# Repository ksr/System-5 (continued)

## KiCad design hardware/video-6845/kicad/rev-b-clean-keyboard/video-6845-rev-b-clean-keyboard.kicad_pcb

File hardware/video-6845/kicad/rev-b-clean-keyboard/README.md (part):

# 6845 video card Rev B-Clean-Keyboard: KiCad master (2026-11-20)

> **Hand-maintained since 2026-11-20** (`MASTER`), made by `gen/build.sh` from Rev B-Clean's files each run.
> **Not ordered, not built.** Ken, 2026-11-20: "now i want to add keyboard support to Rev B Clean, Call it
> Rev-b-clean-keyboard. Look at video-g for keyboard section only. Expand bus to the 36 pin bus and add jumpers
> required to access keyboard. Rev-b-clean-keyboard and Video-g will never be used at the same time." Asked how the
> CPU should read the keyboard: "Memory-mapped, as VIDEO-G". Later the same day: "ok to grow card if needed", and "it
> is messy to have keyboard and video connector on different edges. Need to move together. Less of an issue for FTDI."
> And: "I would prefer for the power LED to be in the corner like most/all other boards."

Rev B-Clean (`../rev-b-clean/`) is Rev B, the 6845 video card in Ken's machine since 2005, cleaned up for a new order.
This card is Rev B-Clean with a **PS/2 keyboard** on it, so that one card is the whole console: the video as Rev B has
it, and the keyboard section of VIDEO-G TEXT (`hardware/video-g/DESIGN.md`), read the way VIDEO-G's is. It takes the
place of the 2005 IO card's keyboard path (PAK-VI, PIC, CDP1852).

| | Rev B-Clean | Rev B-Clean-Keyboard |
|---|---|---|
| Board | 141.0 x 96.2 mm, 2 layers | **190.5 x 106.565 mm** (7.50 in, the IO panel's length; VIDEO-G TEXT's height), 2 layers: 49.5 mm longer at the front edge for the keyboard section, 10.3 mm more at the +5V end of the bus edge for the six more bus pins |
| Bus connector | 30 pins | **36 pins** (J1): the 30 where they were, then -EF1, -EF2, -EF3, -DMAIN, SC0, -PAUSE |
| The 6845 | answers all of 7800-7FFF (the pair 7800 / 7801, repeated) | **7800 / 7801**, repeated every 8 addresses through 7BFF only; **write-only** (below) |
| Keyboard | none | **PS/2**: an ATmega328P, the key at **7802**, the status at **7804**, KEY-READY also on a bus flag line picked by **JP1** |
| Video jack | RCA on a side edge, where 2005 put it | **RCA at the front edge, under the PS/2 jack** |
| Copper | Rev B's, track for track | Rev B's kept and locked, but for three places (below); the keyboard section's tracks added round it |

## The map (block 7, SV1 as on Rev B)

| Address | Read | Write |
|---|---|---|
| 7000-77FF | the text RAM | the text RAM |
| 7800 / 7801 | nothing (FF on the bus Rev D): the 6845 is write-only | the 6845's address register / data |
| 7802 | **the key**; the read clears KEY-READY (at TPB) | nothing |
| 7804 | **status**: bit 0 KEY-READY, bit 2 VSYNC, bit 3 DE, bit 7 = 1, the rest 0 | nothing |
| 7806, 7C00-7FFF | nothing (VIDEO-G has its mouse, Y register and graphics window there) | nothing |

**The 6845 is write-only** (Ken, 2026-11-24: "Write-only"; [below](#the-6845-is-write-only-2026-11-24)). Nothing of System-5's
reads its registers: not HBIOS, GBASIC or Elf/OS (looked for in the sources, and watched in the emulator). The RAM probes of
HBIOS and of the Elf/OS kernel read 7800, find no RAM there, and need nothing of it. VSYNC and DE are in the status byte.

7800-7807 repeat every 8 addresses through 7BFF. The key and the status are where VIDEO-G TEXT has them, with the same
bits, so **the VIDEO-G HBIOS runs on this card as it is** (`firmware/hbios/video-g`: it polls 7804 and reads 7802). Its
6845 table (64 x 25, eight lines a row, a 1.5 MHz character clock) fits Rev B's hardware too: 9 MHz divided by 6 is
1.5 MHz, and Rev B's character ROM has eight lines a character. In the emulator the monitor comes up on 25 rows and
Elf/OS 5.1.1 boots (below). The machine's own HBIOS (v1.0.x) would show the video but look for keys on port 1.

## Jumpers and connectors

- **SV1 ADDRESS BLOCK**, as on Rev B: one shunt on A15 (pins 1-2) puts the card at 7000.
- **JP1 KBD FLAG** (2 x 4, at the top edge as drawn, by the bus connector's new pins): one shunt picks the bus line
  that KEY-READY pulls low, **-EF1, -EF2, -EF3 or -EF**, or none. The VIDEO-G HBIOS does not need it (it reads the
  status register); a program that tests a flag does. On CPU Rev D the line then goes to whichever of EF1-EF4 that
  card's own jumpers give it.
- **J3**, PS/2 keyboard (Mini-DIN-6), and **J2**, composite video (RCA), side by side at the front edge, mouths at the
  edge. **J4**, the FTDI header for the ATmega's bootloader, lies along the bottom edge as drawn, near the front
  (pin 1 GND at the bus end ... pin 6 DTR, both named on the board).
- **Which backplane:** the 36-pin connector is for the bus Rev D (`hardware/bus/kicad/rev-d`), whose slots have the
  six more positions and pull-ups on -EF1 to -EF3. Pads 1-30 are on Rev B's holes, so with a 30-pin header fitted
  there instead the card is a 30-pin card, flag on -EF only (R11 pulls -EF up on the card). That has not been tried,
  and the card is 10 mm taller than Rev B at that end.

## The keyboard section

It is VIDEO-G TEXT's, part for part and pin for pin (`gen/keyboard.py` has the list), so the ATmega's firmware is the
same sketch, `embedded/video-g-ps2`, in its keyboard mode (PD7 open):

- **IC21 ATmega328P** (Y1 16 MHz) reads the PS/2 keyboard and puts each key's code on MD0-MD7; its LDDATA edge clocks
  the code into **IC19** (74HCT374, the key latch) and sets KEY-READY (**IC18**, half a 74HCT74).
- **IC15** (74HCT138) is the one new decoder: enabled by Rev B's upper-half select (the net that was the 6845's -CS,
  now -UPPER) and A10 low, it picks by A1-A2 the 6845, the key or the status. **IC16** (74HCT32) makes the two read
  enables with -MRD, and the key-read strobe at TPB; **IC17** (74HCT00) inverts TPB and -RESET and makes the
  KEY-READY clear. **IC20** (74HCT244) puts the status on the bus.
- **IC18's other half is the 6845's E** (below).
- **IC22 is a second 7416** (open-collector inverters), for the two jobs VIDEO-G TEXT gives to its 7416, on the same
  gates: one pulls the flag line low while KEY-READY, one pulls the ATmega's reset low while the bus -RESET is low.
  The other four gates' inputs are on ground. Rev B's own 7416 (IC14) has three spare gates, but their inputs are
  tied to ground by copper that carries ground on to other parts, so using them would have meant cutting Rev B's
  ground. The card was first drawn with two 2N7000 transistors there; Ken, 2026-11-20: "swap". A 7406, a 7405 or a
  74HC05 has the same pins and does the same in this socket.
- F1 (0.5 A PTC) feeds the keyboard's +5 V; R8, R9 (4.7k) pull up its clock and data.

Like VIDEO-G TEXT's decoder, IC15 sees the high address byte on A1-A2 early in each cycle. For the addresses the
software uses (7800-7807) that early pick is the 6845, whose E (CRTE) is still low; KEY-READY is cleared only at TPB.

## The 6845 is write-only (2026-11-24)

Rev B wires the 6845's R/W to -MRW and its E to TPB. Two faults come with that (`hardware/TIMING-REVIEW.md`, T2; the first
was seen on the bus of the built card):

- **F1:** -MRW rises half a clock before TPB falls, so every register write ends in a read: the 6845 and the 1802 both
  drive the data bus, and a 6845 that takes its byte when E falls is not written at all.
- **F2:** nothing of -MRD is in its select, so it drives the bus at TPB of a cycle with no memory access (GLO, GHI, PLO,
  PHI, SEP, SEX) when that register points at it.

Ken, 2026-11-24: "Fix both boards", and, asked whether to keep the register reads: "Write-only". On this card:

- **R/W (IC3 pin 22) is on ground**, and **E (pin 23) is CRTE = NOT -MRW**: high for the whole write strobe, 5 T to 7 T,
  and at no other time. So the 6845 never drives the bus, whatever the cycle.
- CRTE is **IC18A**, the spare half of the KEY-READY 74HCT74, as an inverter: its -CLR (pin 1) on ground and -MRW on its
  -PRE (pin 4) make Q (pin 5) high while -MRW is low and low otherwise. It has no state to power up in. (Its D and clock stay
  on ground.)
- E is two clocks long and the data stays until T - 200 ns past it, so **every grade on the two data sheets here will do, at 2 MHz too**
  (Motorola's 1 MHz part, Hitachi's 1, 1.5 and 2 MHz). Motorola's allows E high for 25 us at most, Hitachi's has no limit: a pause, stepping and the bus driver hold it longer
  (`hardware/TIMING-REVIEW.md`, "E held high"). From the netlist
  at 2 MHz, worst case (`python3 -m s5emu.timing --crtc B-Clean-Keyboard 2`): E's width +406 ns for a 1 MHz 6845 (+636 for an HD68B45), data
  hold +246, data set-up +2055, address set-up +895.
- `software/s5emu/tests/test_hw_crtcbus.py` holds it: the two faults' tests fail on the card as first drawn and pass here,
  and nine wrong wires of the change are each caught.

The register reads that are lost (R14-R17) were never used; on the 1 MHz part they were late by 77 ns in the worst case.

## Where Rev B's copper was touched

Of Rev B-Clean's 1,415 tracks and vias, 1,390 are where 2005 put them, locked, and `gen/make_board.py` stops if any
pad of Rev B's would change its net. The other 25:

1. **The 6845's select** (5 pieces). Rev B's track from IC5 pin 3 to IC3 pin 25 is cut at IC5: the pin now drives
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
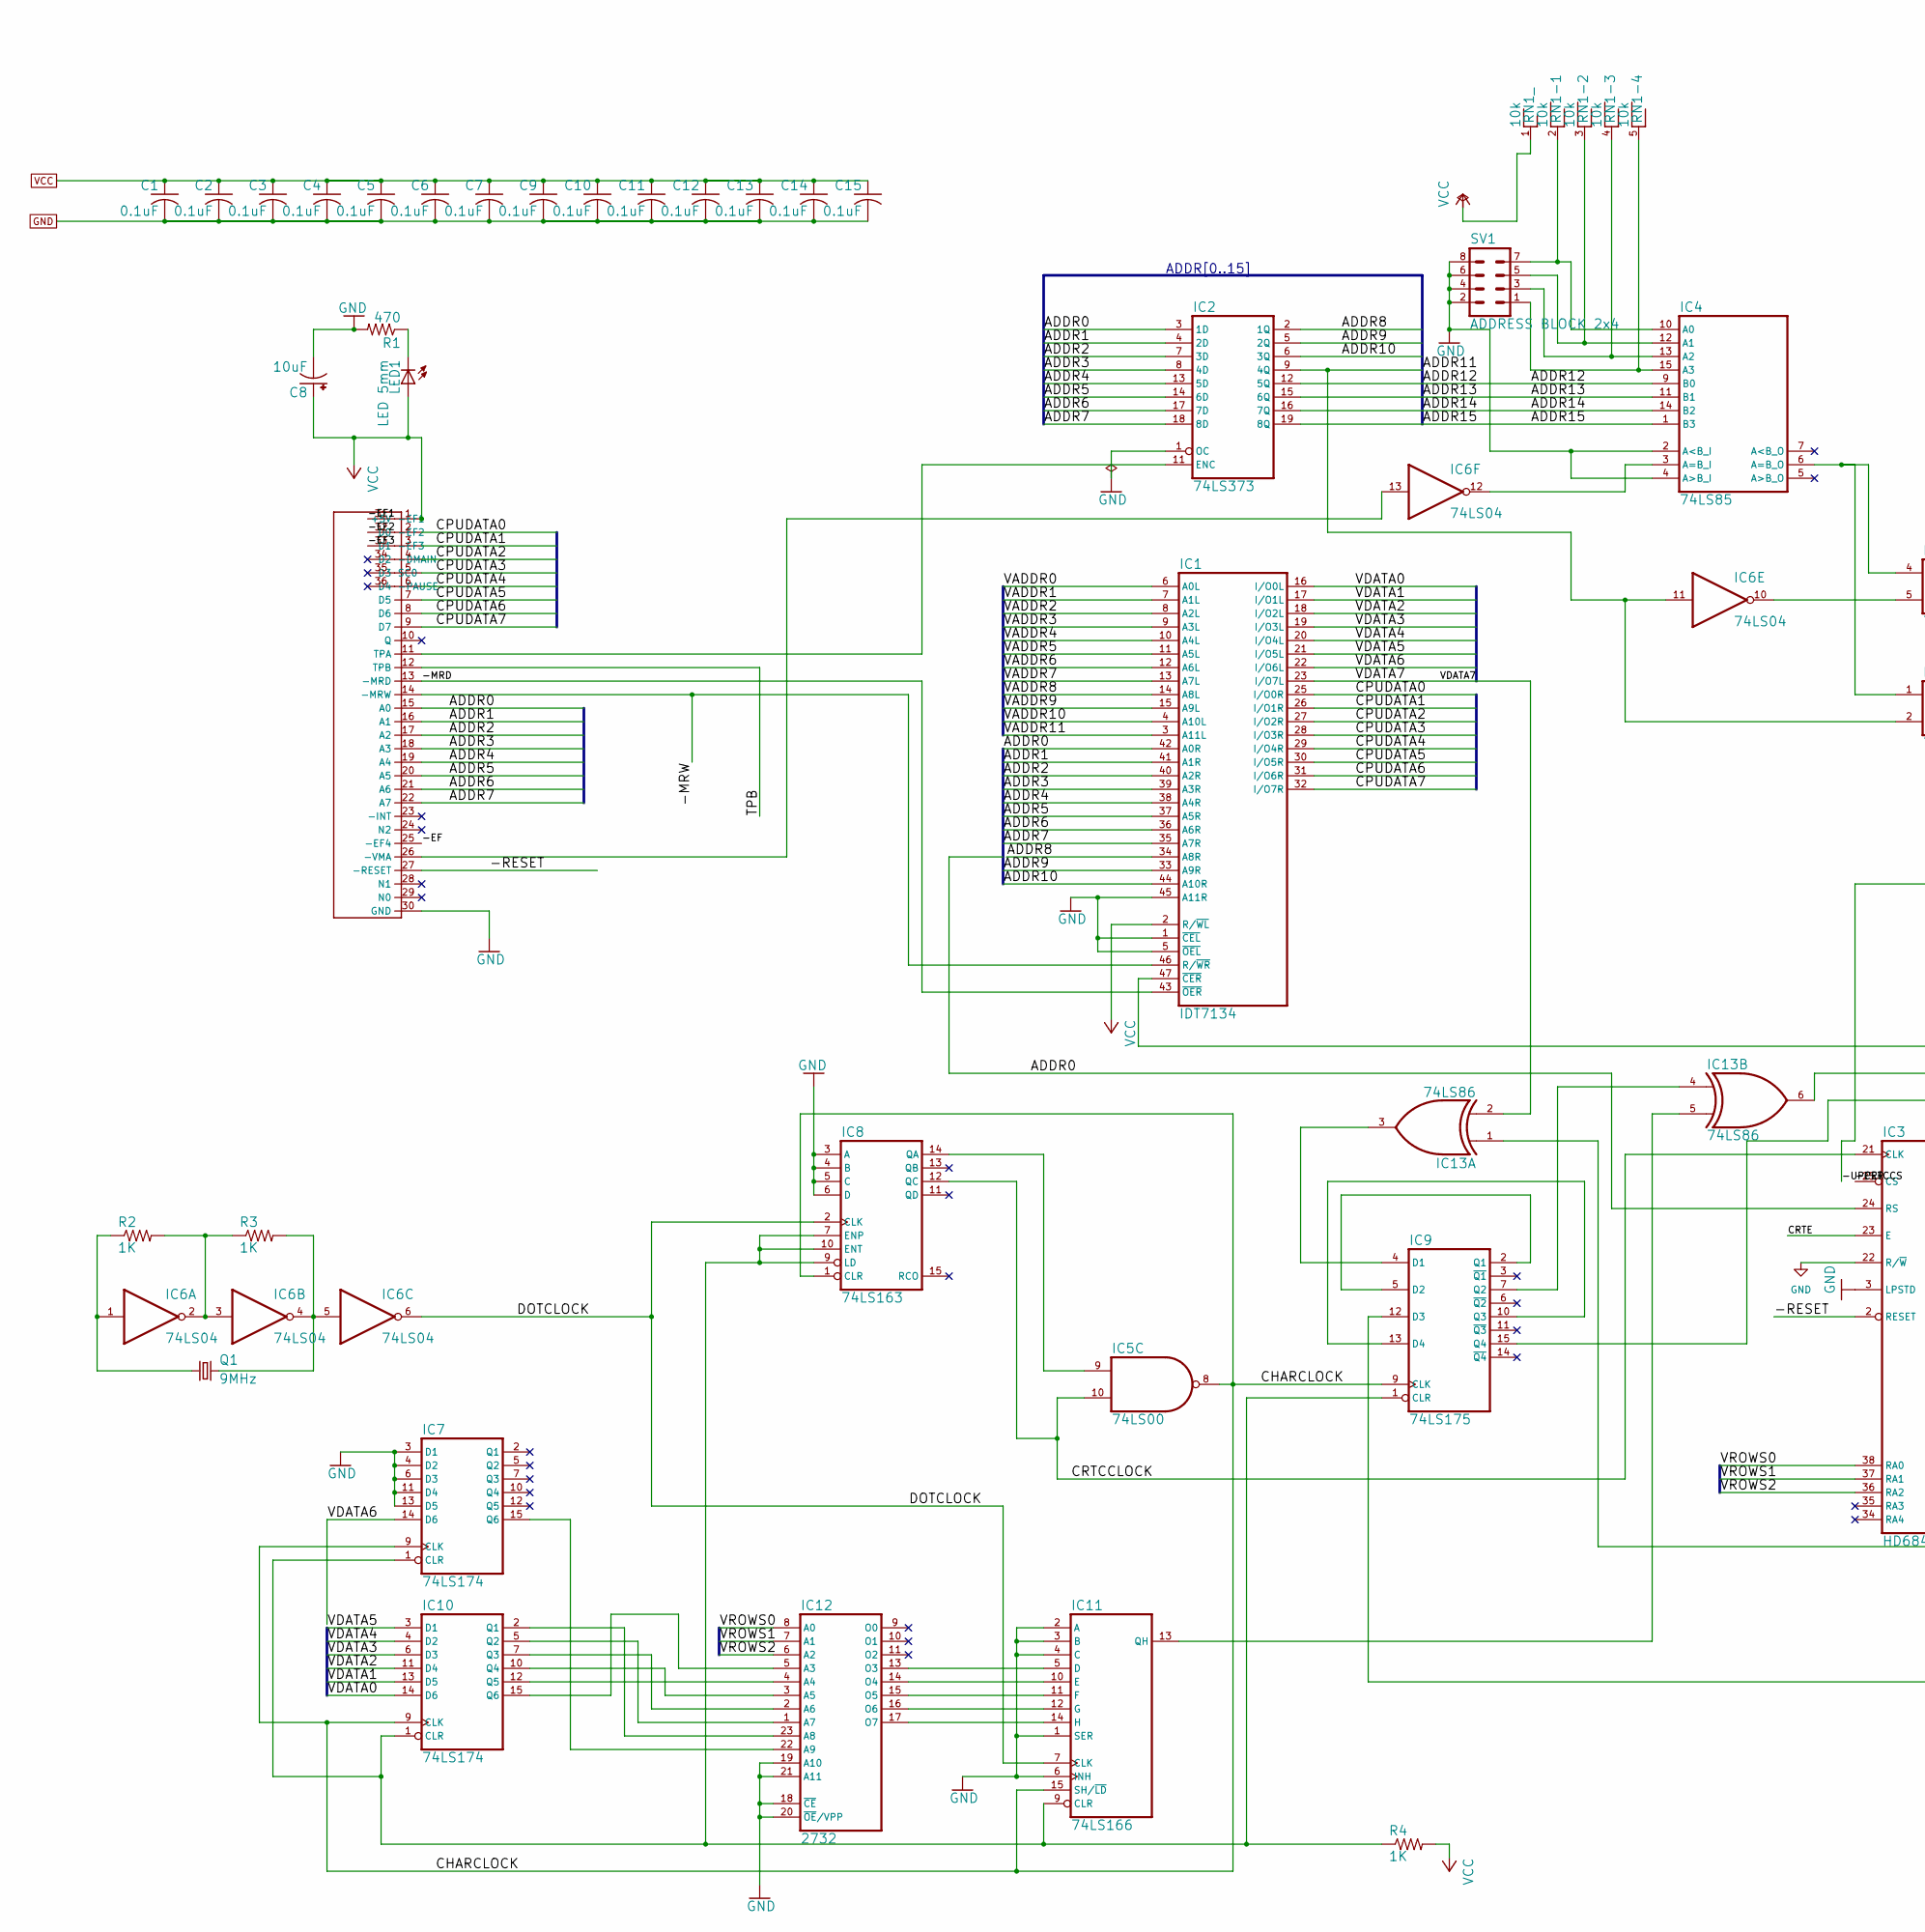
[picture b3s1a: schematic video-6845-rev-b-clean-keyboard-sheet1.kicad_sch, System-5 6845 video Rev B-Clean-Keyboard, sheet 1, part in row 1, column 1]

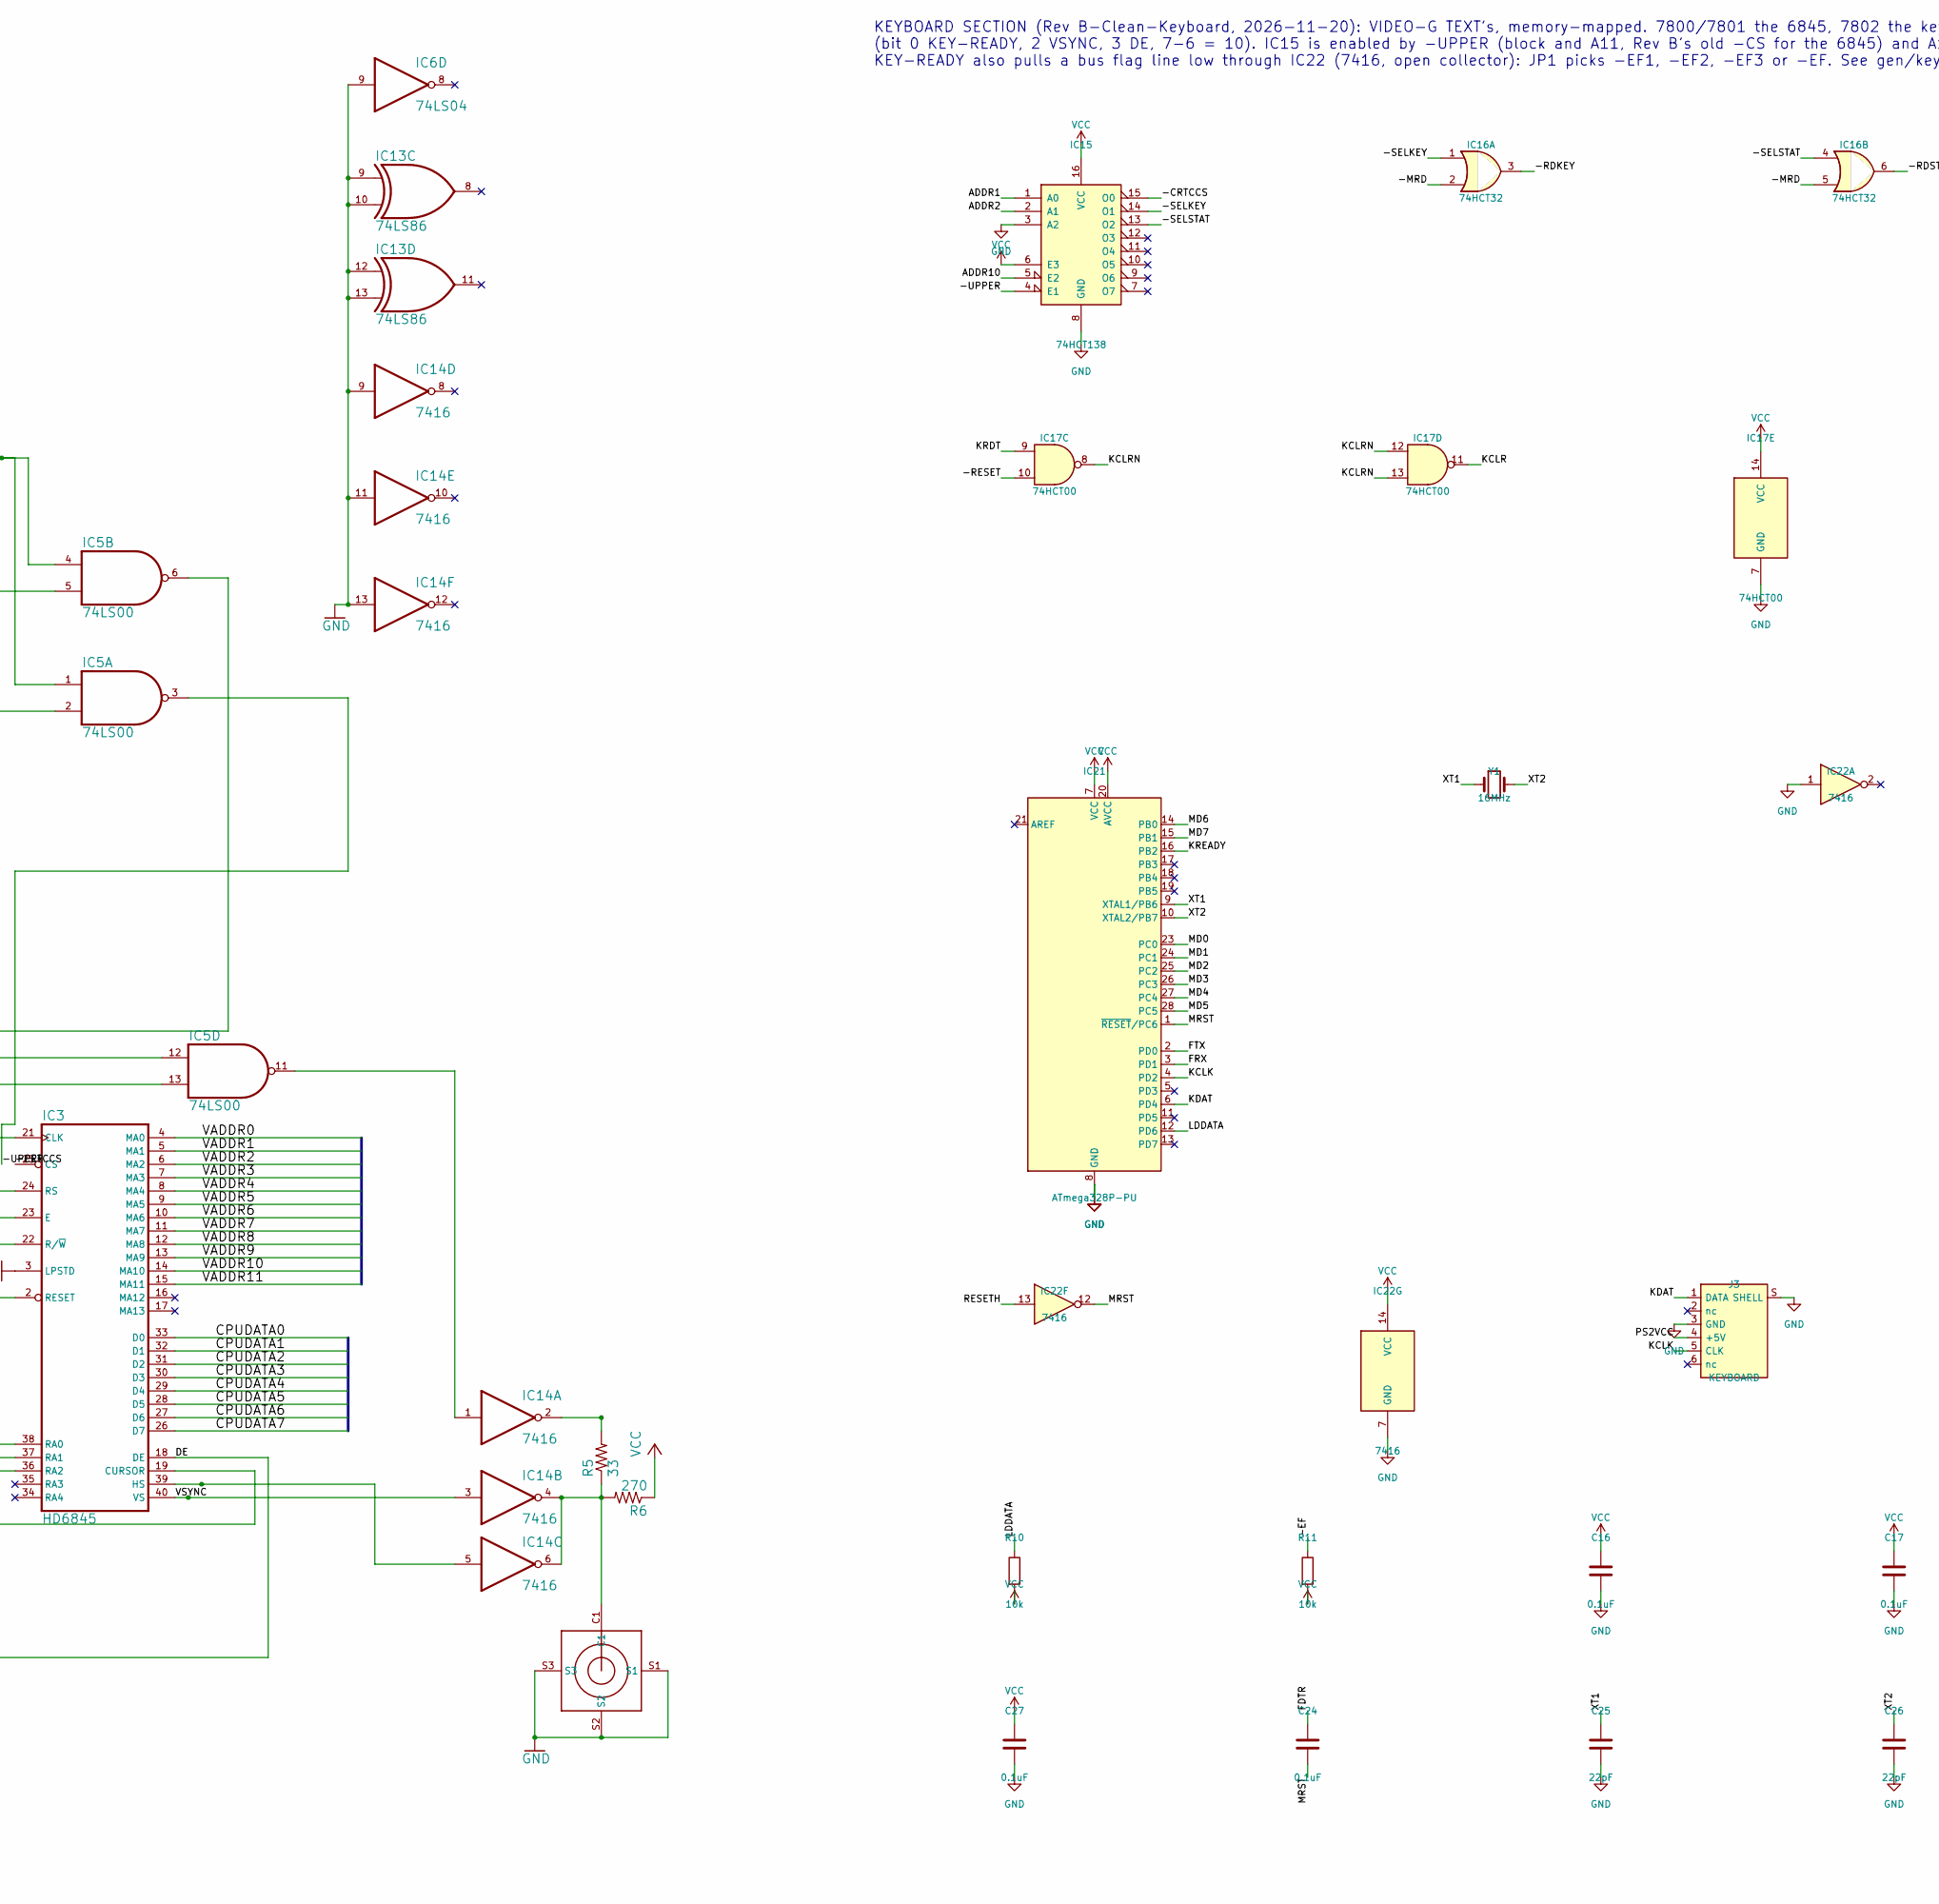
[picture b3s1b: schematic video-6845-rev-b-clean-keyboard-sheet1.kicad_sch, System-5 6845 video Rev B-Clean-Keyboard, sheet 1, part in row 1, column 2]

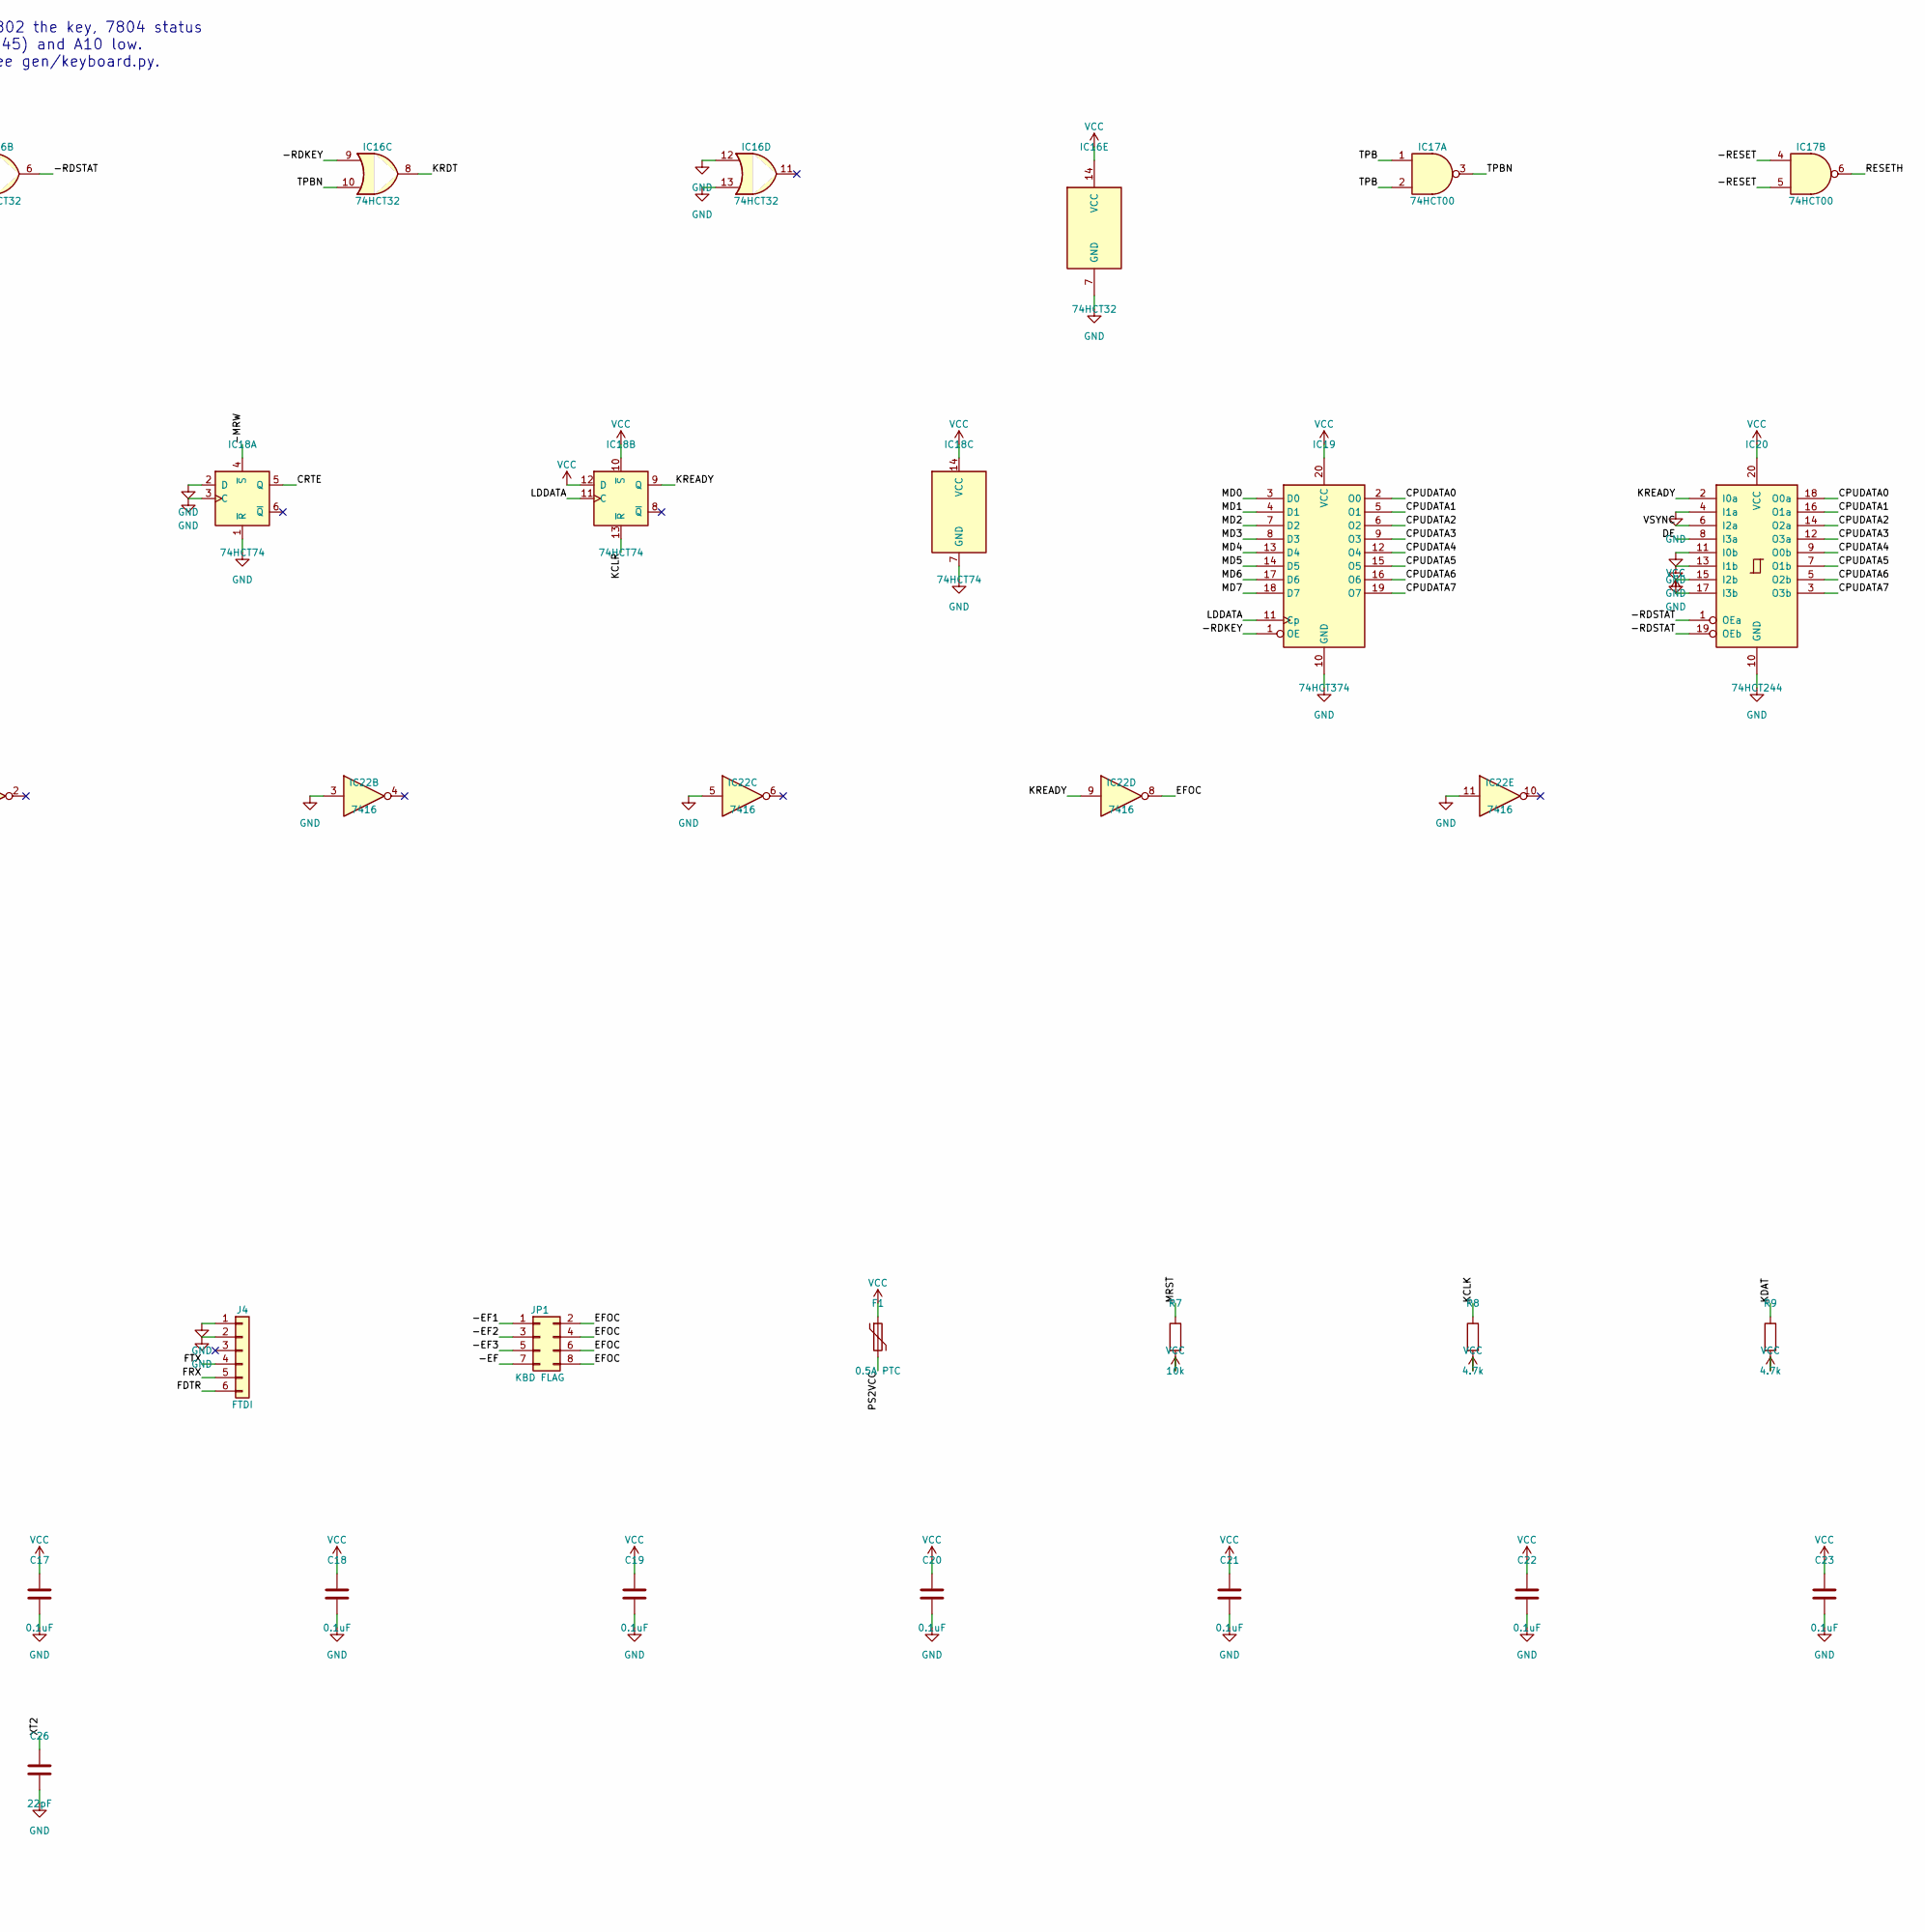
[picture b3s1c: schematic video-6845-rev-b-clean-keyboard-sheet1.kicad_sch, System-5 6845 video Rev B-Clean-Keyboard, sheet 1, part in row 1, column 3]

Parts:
C1, C2, C3, C4, C5, C6, C7, C9, C10, C11, C12, C13, C14, C15, C16, C17, C18, C19, C20, C21, C22, C23, C24, C27: 0.1uF; C025-050X050
C8: 10uF; E2,5-7
C25, C26: 22pF; C025-050X050
F1: 0.5A PTC; Fuse_Bourns_MF-RHT050
IC1: IDT7134; DIL48
IC2: 74LS373; DIL20
IC3: HD6845; DIL40
IC4: 74LS85; DIL16
IC5: 74LS00; DIL14
IC6: 74LS04; DIL14
IC7, IC10: 74LS174; DIL16
IC8: 74LS163; DIL16
IC9: 74LS175; DIL16
IC11: 74LS166; DIL16
IC12: 2732; DIL24
IC13: 74LS86; DIL14
IC14: 7416; DIL14
IC15: 74HCT138; DIP-16_W7.62mm_Socket
IC16: 74HCT32; DIP-14_W7.62mm_Socket
IC17: 74HCT00; DIP-14_W7.62mm_Socket
IC18: 74HCT74; DIP-14_W7.62mm_Socket
IC19: 74HCT374; DIP-20_W7.62mm_Socket
IC20: 74HCT244; DIP-20_W7.62mm_Socket
IC21: ATmega328P-PU; DIP-28_W7.62mm_Socket
IC22: 7416; DIP-14_W7.62mm_Socket
J1: System-5 bus 36-pin; C36
J2: RCA jack; RCA
J3: KEYBOARD; MiniDIN6_MD-60SM
J4: FTDI; PinHeader_1x06_P2.54mm_Vertical
JP1: KBD FLAG; PinHeader_2x04_P2.54mm_Vertical
LED1: LED 5mm; LED5MM
Q1: 9MHz; HC49U-V
R1: 470; 0207_7
R2, R3, R4: 1K; 0207_7
R5: 33; 0207_7
R6: 270; 0207_7
R7, R10, R11: 10k; R_Axial_DIN0207_L6.3mm_D2.5mm_P2.54mm_Vertical
R8, R9: 4.7k; R_Axial_DIN0207_L6.3mm_D2.5mm_P2.54mm_Vertical
RN1: 10k; RN-5
SV1: ADDRESS BLOCK 2x4; MA04-2
Y1: 16MHz; Crystal_HC49-U_Vertical

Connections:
/Sheet 1/-CRTCCS: IC3.25 (CS), IC15.15 (O0)
/Sheet 1/-EF: J1.25 (-EF4), JP1.7, R11.1
/Sheet 1/-EF1: J1.31 (-EF1), JP1.1
/Sheet 1/-EF2: J1.32 (-EF2), JP1.3
/Sheet 1/-EF3: J1.33 (-EF3), JP1.5
/Sheet 1/-MRD: IC1.43 (~OER), IC16.2, IC16.5, J1.13 (-MRD)
/Sheet 1/-MRW: IC1.46 (R/~WR), IC18.4 (~S), J1.14 (-MRW)
/Sheet 1/-RDKEY: IC16.3, IC16.9, IC19.1 (OE)
/Sheet 1/-RDSTAT: IC16.6, IC20.1 (OEa), IC20.19 (OEb)
/Sheet 1/-RESET: IC3.2 (RESET), IC17.4, IC17.5, IC17.10, J1.27 (-RESET)
/Sheet 1/-SELKEY: IC15.14 (O1), IC16.1
/Sheet 1/-SELSTAT: IC15.13 (O2), IC16.4
/Sheet 1/-UPPER: IC5.3 (O), IC15.4 (E1)
/Sheet 1/ADDR0: IC1.42 (A0R), IC2.3 (1D), IC3.24 (RS), J1.15 (A0)
/Sheet 1/ADDR1: IC1.41 (A1R), IC2.4 (2D), IC15.1 (A0), J1.16 (A1)
/Sheet 1/ADDR2: IC1.40 (A2R), IC2.7 (3D), IC15.2 (A1), J1.17 (A2)
/Sheet 1/ADDR3: IC1.39 (A3R), IC2.8 (4D), J1.18 (A3)
/Sheet 1/ADDR4: IC1.38 (A4R), IC2.13 (5D), J1.19 (A4)
/Sheet 1/ADDR5: IC1.37 (A5R), IC2.14 (6D), J1.20 (A5)
/Sheet 1/ADDR6: IC1.36 (A6R), IC2.17 (7D), J1.21 (A6)
/Sheet 1/ADDR7: IC1.35 (A7R), IC2.18 (8D), J1.22 (A7)
/Sheet 1/ADDR8: IC1.34 (A8R), IC2.2 (1Q)
/Sheet 1/ADDR9: IC1.33 (A9R), IC2.5 (2Q)
/Sheet 1/ADDR10: IC1.44 (A10R), IC2.6 (3Q), IC15.5 (E2)
/Sheet 1/ADDR11: IC2.9 (4Q), IC5.2 (I1), IC6.11 (I)
/Sheet 1/ADDR12: IC2.12 (5Q), IC4.9 (B0)
/Sheet 1/ADDR13: IC2.15 (6Q), IC4.11 (B1)
/Sheet 1/ADDR14: IC2.16 (7Q), IC4.14 (B2)
/Sheet 1/ADDR15: IC2.19 (8Q), IC4.1 (B3)
/Sheet 1/CHARCLOCK: IC5.8 (O), IC7.9 (CLK), IC8.1 (CLR), IC9.9 (CLK), IC10.9 (CLK), IC11.15 (SH/~LD)
/Sheet 1/CPUDATA0: IC1.25 (I/O0R), IC3.33 (D0), IC19.2 (O0), IC20.18 (O0a), J1.2 (D0)
/Sheet 1/CPUDATA1: IC1.26 (I/O1R), IC3.32 (D1), IC19.5 (O1), IC20.16 (O1a), J1.3 (D1)
/Sheet 1/CPUDATA2: IC1.27 (I/O2R), IC3.31 (D2), IC19.6 (O2), IC20.14 (O2a), J1.4 (D2)
/Sheet 1/CPUDATA3: IC1.28 (I/O3R), IC3.30 (D3), IC19.9 (O3), IC20.12 (O3a), J1.5 (D3)
/Sheet 1/CPUDATA4: IC1.29 (I/O4R), IC3.29 (D4), IC19.12 (O4), IC20.9 (O0b), J1.6 (D4)
/Sheet 1/CPUDATA5: IC1.30 (I/O5R), IC3.28 (D5), IC19.15 (O5), IC20.7 (O1b), J1.7 (D5)
/Sheet 1/CPUDATA6: IC1.31 (I/O6R), IC3.27 (D6), IC19.16 (O6), IC20.5 (O2b), J1.8 (D6)
/Sheet 1/CPUDATA7: IC1.32 (I/O7R), IC3.26 (D7), IC19.19 (O7), IC20.3 (O3b), J1.9 (D7)
/Sheet 1/CRTCCLOCK: IC3.21 (CLK), IC5.10 (I1), IC8.12 (QC)
/Sheet 1/CRTE: IC3.23 (E), IC18.5 (Q)
/Sheet 1/DE: IC3.18 (DE), IC9.12 (D3), IC20.8 (I3a)
/Sheet 1/DOTCLOCK: IC6.6 (O), IC8.2 (CLK), IC11.7 (CLK)
/Sheet 1/EFOC: IC22.8, JP1.2, JP1.4, JP1.6, JP1.8
/Sheet 1/FDTR: C24.1, J4.6
/Sheet 1/FRX: IC21.3 (PD1), J4.5
/Sheet 1/FTX: IC21.2 (PD0), J4.4
/Sheet 1/KCLK: IC21.4 (PD2), J3.5 (CLK), R8.1
/Sheet 1/KCLR: IC17.11, IC18.13 (~R)
/Sheet 1/KCLRN: IC17.8, IC17.12, IC17.13
/Sheet 1/KDAT: IC21.6 (PD4), J3.1 (DATA), R9.1
/Sheet 1/KRDT: IC16.8, IC17.9
/Sheet 1/KREADY: IC18.9 (Q), IC20.2 (I0a), IC21.16 (PB2), IC22.9
/Sheet 1/LDDATA: IC18.11 (C), IC19.11 (Cp), IC21.12 (PD6), R10.1
/Sheet 1/MD0: IC19.3 (D0), IC21.23 (PC0)
/Sheet 1/MD1: IC19.4 (D1), IC21.24 (PC1)
/Sheet 1/MD2: IC19.7 (D2), IC21.25 (PC2)
/Sheet 1/MD3: IC19.8 (D3), IC21.26 (PC3)
/Sheet 1/MD4: IC19.13 (D4), IC21.27 (PC4)
/Sheet 1/MD5: IC19.14 (D5), IC21.28 (PC5)
/Sheet 1/MD6: IC19.17 (D6), IC21.14 (PB0)
/Sheet 1/MD7: IC19.18 (D7), IC21.15 (PB1)
/Sheet 1/MRST: C24.2, IC21.1 (~RESET/PC6), IC22.12, R7.1
/Sheet 1/PS2VCC: F1.2, J3.4 (+5V)
/Sheet 1/RESETH: IC17.6, IC22.13
/Sheet 1/TPB: IC17.1, IC17.2, J1.12 (TPB)
/Sheet 1/TPBN: IC16.10, IC17.3
/Sheet 1/VADDR0: IC1.6 (A0L), IC3.4 (MA0)
/Sheet 1/VADDR1: IC1.7 (A1L), IC3.5 (MA1)
/Sheet 1/VADDR2: IC1.8 (A2L), IC3.6 (MA2)
/Sheet 1/VADDR3: IC1.9 (A3L), IC3.7 (MA3)
/Sheet 1/VADDR4: IC1.10 (A4L), IC3.8 (MA4)
/Sheet 1/VADDR5: IC1.11 (A5L), IC3.9 (MA5)
/Sheet 1/VADDR6: IC1.12 (A6L), IC3.10 (MA6)
/Sheet 1/VADDR7: IC1.13 (A7L), IC3.11 (MA7)
/Sheet 1/VADDR8: IC1.14 (A8L), IC3.12 (MA8)
/Sheet 1/VADDR9: IC1.15 (A9L), IC3.13 (MA9)
/Sheet 1/VADDR10: IC1.4 (A10L), IC3.14 (MA10)
/Sheet 1/VADDR11: IC1.3 (A11L), IC3.15 (MA11)
/Sheet 1/VDATA0: IC1.16 (I/O0L), IC10.14 (D6)
/Sheet 1/VDATA1: IC1.17 (I/O1L), IC10.13 (D5)
/Sheet 1/VDATA2: IC1.18 (I/O2L), IC10.11 (D4)
/Sheet 1/VDATA3: IC1.19 (I/O3L), IC10.6 (D3)
/Sheet 1/VDATA4: IC1.20 (I/O4L), IC10.4 (D2)
/Sheet 1/VDATA5: IC1.21 (I/O5L), IC10.3 (D1)
/Sheet 1/VDATA6: IC1.22 (I/O6L), IC7.14 (D6)
/Sheet 1/VDATA7: IC1.23 (I/O7L), IC13.2 (I1)
/Sheet 1/VROWS0: IC3.38 (RA0), IC12.8 (A0)
/Sheet 1/VROWS1: IC3.37 (RA1), IC12.7 (A1)
/Sheet 1/VROWS2: IC3.36 (RA2), IC12.6 (A2)
/Sheet 1/VSYNC: IC3.40 (VS), IC14.3 (I), IC20.6 (I2a)
/Sheet 1/XT1: C25.1, IC21.9 (XTAL1/PB6), Y1.1
/Sheet 1/XT2: C26.1, IC21.10 (XTAL2/PB7), Y1.2
GND: C1.2, C2.2, C3.2, C4.2, C5.2, C6.2, C7.2, C8.-, C9.2, C10.2, C11.2, C12.2, C13.2, C14.2, C15.2, C16.2, C17.2, C18.2, C19.2, C20.2, C21.2, C22.2, C23.2, C25.2, C26.2, C27.2, IC1.1 (~CEL), IC1.5 (~OEL), IC1.24 (GND), IC1.45 (A11R), IC2.1 (OC), IC2.10 (GND), IC3.1 (GND), IC3.3 (LPSTD), IC3.22 (R/~W), IC4.2 (A<B_I), IC4.4 (A>B_I), IC4.8 (GND), IC5.7 (GND), IC6.7 (GND), IC6.9 (I), IC7.3 (D1), IC7.4 (D2), IC7.6 (D3), IC7.8 (GND), IC7.11 (D4), IC7.13 (D5), IC8.3 (A), IC8.4 (B), IC8.5 (C), IC8.6 (D), IC8.8 (GND), IC9.8 (GND), IC10.8 (GND), IC11.1 (SER), IC11.2 (A), IC11.3 (B), IC11.4 (C), IC11.6 (INH), IC11.8 (GND), IC12.12 (GND), IC12.18 (~CE), IC12.19 (A10), IC12.20 (~OE/VPP), IC12.21 (A11), IC13.7 (GND), IC13.9 (I0), IC13.10 (I1), IC13.12 (I0), IC13.13 (I1), IC14.7 (GND), IC14.9 (I), IC14.11 (I), IC14.13 (I), IC15.3 (A2), IC15.8 (GND), IC16.7 (GND), IC16.12, IC16.13, IC17.7 (GND), IC18.1 (~R), IC18.2 (D), IC18.3 (C), IC18.7 (GND), IC19.10 (GND), IC20.4 (I1a), IC20.10 (GND), IC20.11 (I0b), IC20.13 (I1b), IC20.15 (I2b), IC21.8 (GND), IC21.22 (GND), IC22.1, IC22.3, IC22.5, IC22.7 (GND), IC22.11, J1.30 (GND), J2.S1, J2.S2, J2.S3, J3.3 (GND), J3.S (SHELL), J4.1, J4.2, R1.2, SV1.2, SV1.4, SV1.6, SV1.8
unnamed: IC1.47 (~CER), IC5.6 (O)
unnamed: IC2.11 (ENC), J1.11 (TPA)
unnamed: IC4.10 (A0), RN1.2, SV1.7
unnamed: IC4.12 (A1), RN1.3, SV1.5
unnamed: IC4.13 (A2), RN1.4, SV1.3
unnamed: IC4.15 (A3), RN1.5, SV1.1
unnamed: IC4.3 (A=B_I), IC6.12 (O)
unnamed: IC4.6 (A=B_O), IC5.1 (I0), IC5.4 (I0)
unnamed: IC5.5 (I1), IC6.10 (O)
unnamed: IC5.9 (I0), IC8.14 (QA)
unnamed: IC5.13 (I1), IC9.15 (Q4)
unnamed: IC6.1 (I), Q1.1, R2.1
unnamed: IC6.2 (O), IC6.3 (I), R2.2, R3.1
unnamed: IC6.4 (O), IC6.5 (I), Q1.2, R3.2
unnamed: IC6.13 (I), J1.26 (-VMA)
unnamed: IC9.2 (Q1), IC9.5 (D2)
unnamed: IC9.10 (Q3), IC9.13 (D4)
unnamed: IC7.1 (CLR), IC8.7 (ENP), IC8.9 (LD), IC8.10 (ENT), IC9.1 (CLR), IC10.1 (CLR), IC11.9 (CLR), R4.1
unnamed: IC10.2 (Q1), IC12.23 (A8)
unnamed: IC10.5 (Q2), IC12.1 (A7)
unnamed: IC10.7 (Q3), IC12.2 (A6)
unnamed: IC10.10 (Q4), IC12.3 (A5)
unnamed: IC10.12 (Q5), IC12.4 (A4)
unnamed: IC10.15 (Q6), IC12.5 (A3)
unnamed: IC11.5 (D), IC12.13 (O3)
unnamed: IC11.10 (E), IC12.14 (O4)
unnamed: IC11.11 (F), IC12.15 (O5)
unnamed: IC11.12 (G), IC12.16 (O6)
unnamed: IC11.14 (H), IC12.17 (O7)
unnamed: IC11.13 (QH), IC13.5 (I1)
unnamed: IC7.15 (Q6), IC12.22 (A9)
unnamed: IC3.19 (CURSOR), IC13.1 (I0)
unnamed: IC9.4 (D1), IC13.3 (O)
unnamed: IC9.7 (Q2), IC13.4 (I0)
unnamed: IC5.12 (I0), IC13.6 (O)
unnamed: IC5.11 (O), IC14.1 (I)
unnamed: IC14.2 (O), R5.2
unnamed: IC14.4 (O), IC14.6 (O), J2.C1, R5.1, R6.2
unnamed: IC3.39 (HS), IC14.5 (I)
unnamed: LED1.K (C), R1.1
VCC: C1.1, C2.1, C3.1, C4.1, C5.1, C6.1, C7.1, C8.+, C9.1, C10.1, C11.1, C12.1, C13.1, C14.1, C15.1, C16.1, C17.1, C18.1, C19.1, C20.1, C21.1, C22.1, C23.1, C27.1, F1.1, IC1.2 (R/~WL), IC1.48 (VCC), IC2.20 (VCC), IC3.20 (VCC), IC4.16 (VCC), IC5.14 (VCC), IC6.14 (VCC), IC7.16 (VCC), IC8.16 (VCC), IC9.16 (VCC), IC10.16 (VCC), IC11.16 (VCC), IC12.24 (VCC), IC13.14 (VCC), IC14.14 (VCC), IC15.6 (E3), IC15.16 (VCC), IC16.14 (VCC), IC17.14 (VCC), IC18.10 (~S), IC18.12 (D), IC18.14 (VCC), IC19.20 (VCC), IC20.17 (I3b), IC20.20 (VCC), IC21.7 (VCC), IC21.20 (AVCC), IC22.14 (VCC), J1.1 (+5V), LED1.A, R4.2, R6.1, R7.2, R8.2, R9.2, R10.2, R11.2, RN1.1

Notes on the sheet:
ADDR[0..15]
KEYBOARD SECTION (Rev B-Clean-Keyboard, 2026-11-20): VIDEO-G TEXT's, memory-mapped. 7800/7801 the 6845, 7802 the key, 7804 status
(bit 0 KEY-READY, 2 VSYNC, 3 DE, 7-6 = 10). IC15 is enabled by -UPPER (block and A11, Rev B's old -CS for the 6845) and A10 low.
KEY-READY also pulls a bus flag line low through IC22 (7416, open collector): JP1 picks -EF1, -EF2, -EF3 or -EF. See gen/keyboard.py.

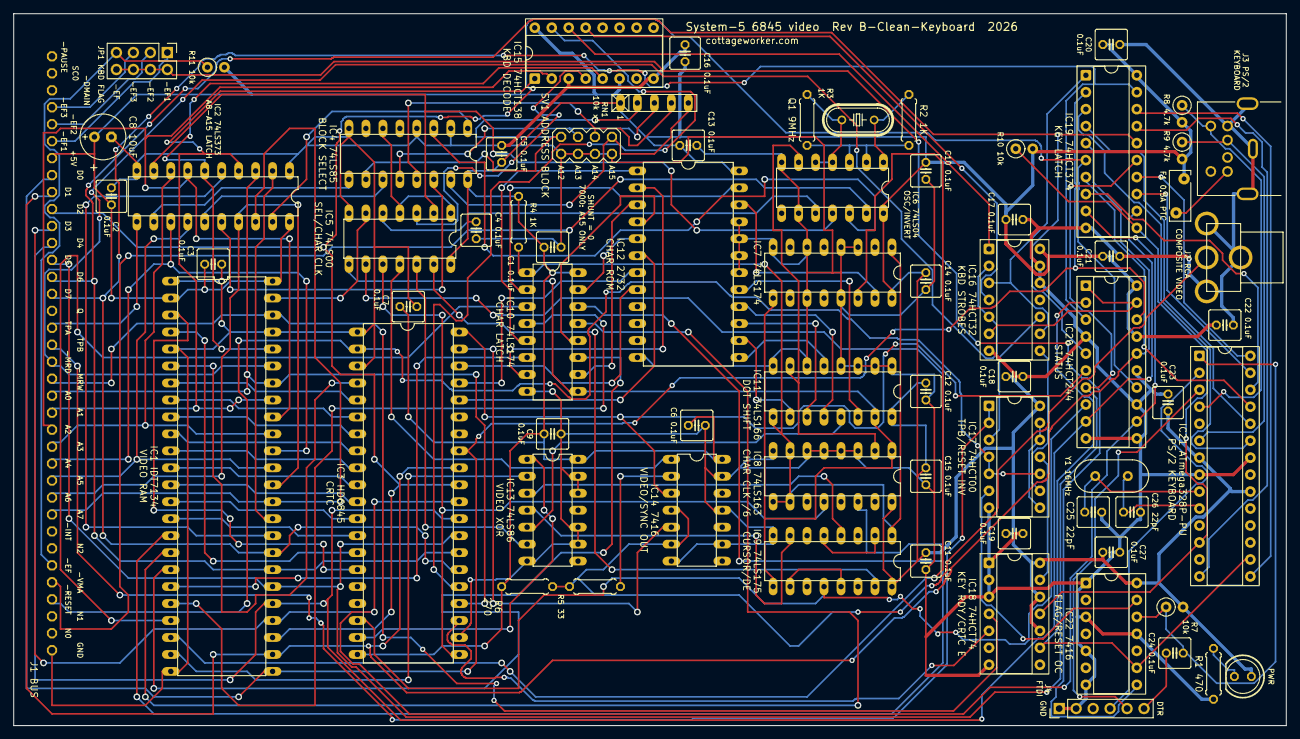
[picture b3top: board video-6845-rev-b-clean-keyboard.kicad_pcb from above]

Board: 2 copper layers, 190.5 x 106.6 mm, 71 parts (0 on the bottom side), 134 nets.

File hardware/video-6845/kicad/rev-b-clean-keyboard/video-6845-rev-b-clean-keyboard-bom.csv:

"Reference","Value","Footprint","QUANTITY"
"C1-C7,C9-C24,C27","0.1uF","video-6845-rev-b-clean-keyboard-eagle:C025-050X050","24"
"C8","10uF","video-6845-rev-b-clean-keyboard-eagle:E2,5-7","1"
"C25,C26","22pF","video-6845-rev-b-clean-keyboard-eagle:C025-050X050","2"
"F1","0.5A PTC","Fuse:Fuse_Bourns_MF-RHT050","1"
"IC1","IDT7134","video-6845-rev-b-clean-keyboard-eagle:DIL48","1"
"IC2","74LS373","video-6845-rev-b-clean-keyboard-eagle:DIL20","1"
"IC3","HD6845","video-6845-rev-b-clean-keyboard-eagle:DIL40","1"
"IC4","74LS85","video-6845-rev-b-clean-keyboard-eagle:DIL16","1"
"IC5","74LS00","video-6845-rev-b-clean-keyboard-eagle:DIL14","1"
"IC6","74LS04","video-6845-rev-b-clean-keyboard-eagle:DIL14","1"
"IC7,IC10","74LS174","video-6845-rev-b-clean-keyboard-eagle:DIL16","2"
"IC8","74LS163","video-6845-rev-b-clean-keyboard-eagle:DIL16","1"
"IC9","74LS175","video-6845-rev-b-clean-keyboard-eagle:DIL16","1"
"IC11","74LS166","video-6845-rev-b-clean-keyboard-eagle:DIL16","1"
"IC12","2732","video-6845-rev-b-clean-keyboard-eagle:DIL24","1"
"IC13","74LS86","video-6845-rev-b-clean-keyboard-eagle:DIL14","1"
"IC14","7416","video-6845-rev-b-clean-keyboard-eagle:DIL14","1"
"IC15","74HCT138","Package_DIP:DIP-16_W7.62mm_Socket","1"
"IC16","74HCT32","Package_DIP:DIP-14_W7.62mm_Socket","1"
"IC17","74HCT00","Package_DIP:DIP-14_W7.62mm_Socket","1"
"IC18","74HCT74","Package_DIP:DIP-14_W7.62mm_Socket","1"
"IC19","74HCT374","Package_DIP:DIP-20_W7.62mm_Socket","1"
"IC20","74HCT244","Package_DIP:DIP-20_W7.62mm_Socket","1"
"IC21","ATmega328P-PU","Package_DIP:DIP-28_W7.62mm_Socket","1"
"IC22","7416","Package_DIP:DIP-14_W7.62mm_Socket","1"
"J1","System-5 bus 36-pin","video-6845-rev-b-clean-keyboard-eagle:C36","1"
"J2","RCA jack","video-6845-rev-b-clean-keyboard-eagle:RCA","1"
"J3","KEYBOARD","video-6845-rev-b-clean-keyboard-eagle:MiniDIN6_MD-60SM","1"
"J4","FTDI","Connector_PinHeader_2.54mm:PinHeader_1x06_P2.54mm_Vertical","1"
"JP1","KBD FLAG","Connector_PinHeader_2.54mm:PinHeader_2x04_P2.54mm_Vertical","1"
"LED1","LED 5mm","video-6845-rev-b-clean-keyboard-eagle:LED5MM","1"
"Q1","9MHz","video-6845-rev-b-clean-keyboard-eagle:HC49U-V","1"
"R1","470","video-6845-rev-b-clean-keyboard-eagle:0207_7","1"
"R2-R4","1K","video-6845-rev-b-clean-keyboard-eagle:0207_7","3"
"R5","33","video-6845-rev-b-clean-keyboard-eagle:0207_7","1"
"R6","270","video-6845-rev-b-clean-keyboard-eagle:0207_7","1"
"R7,R10,R11","10k","Resistor_THT:R_Axial_DIN0207_L6.3mm_D2.5mm_P2.54mm_Vertical","3"
"R8,R9","4.7k","Resistor_THT:R_Axial_DIN0207_L6.3mm_D2.5mm_P2.54mm_Vertical","2"
"RN1","10k","video-6845-rev-b-clean-keyboard-eagle:RN-5","1"
"SV1","ADDRESS BLOCK 2x4","video-6845-rev-b-clean-keyboard-eagle:MA04-2","1"
"Y1","16MHz","Crystal:Crystal_HC49-U_Vertical","1"
